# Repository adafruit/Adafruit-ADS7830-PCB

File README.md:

## Adafruit ADS7830 8-Channel 8-Bit ADC with I2C - STEMMA QT / Qwiic PCB

<a href="http://www.adafruit.com/products/5836"><br/>
Click here to purchase one from the Adafruit shop</a>

PCB files for the Adafruit ADS7830 8-Channel 8-Bit ADC with I2C - STEMMA QT / Qwiic. 

Format is EagleCAD schematic and board layout
* https://www.adafruit.com/product/5836

### Description

Many microcontrollers have ADCs these days, for reading analog/resistive sensors like potentiometers, thermistors, LDR light sensors, etc. but sometimes you need MOAR! Or maybe you're using a single board computer like a Raspberry Pi that has no ADCs at all!

The Adafruit ADS7830 8-Channel 8-Bit ADC with I2C is an affordable 8-channel ADC with I2C interface, so it's easy to include with any platform. Wire up to the SDA/SCL pins plus power and ground, only four wires required. If you need more than 8 channels, there's 2 address pins so you could have 4 x 8 = 32 total ADC channels with chain-able Stemma QT cables.

Note that this chip isn't the fanciest ADC on the market: you can get up 70 Ksamples per second (you'll need 3.4MHz I2C speed support for max speed rate), and only 8-bits of resolution, so it's good for rough sensor measurements. For example, this would definitely be a great way to add a ton of potentiometers or flex sensors to a build, but wouldn't be a good match for precision thermistor conversion.

To use it, check out our Arduino library which will quickly let you read from any of the 8 channels as single ended inputs - or you can use differential mode which will use two adjacent pins for the positive and negative references. You can power the board from 3 or 5V power and logic, which will also act as the reference voltage and pullup voltage. Or you can change the reference voltage by cutting the jumper on the back and wiring to the breakout pad, as long as it is less than the power supply.

To get you going fast, we spun up a custom-made PCB in the STEMMA QT form factor, making it easy to interface with. The STEMMA QT connectors on either side are compatible with the SparkFun Qwiic I2C connectors. This allows you to make solderless connections between your development board and the ADS7830 or to chain it with a wide range of other sensors and accessories using a compatible cable.

QT Cable is not included, but we have a variety in the shop.

Comes with a bit of 0.1" standard header in case you want to use it with a breadboard or perfboard.  Four mounting holes for easy attachment.

### License

Adafruit invests time and resources providing this open source design, please support Adafruit and open-source hardware by purchasing products from [Adafruit](https://www.adafruit.com)!

Designed by Limor Fried/Ladyada for Adafruit Industries.

Creative Commons Attribution/Share-Alike, all text above must be included in any redistribution. 
See license.txt for additional details.

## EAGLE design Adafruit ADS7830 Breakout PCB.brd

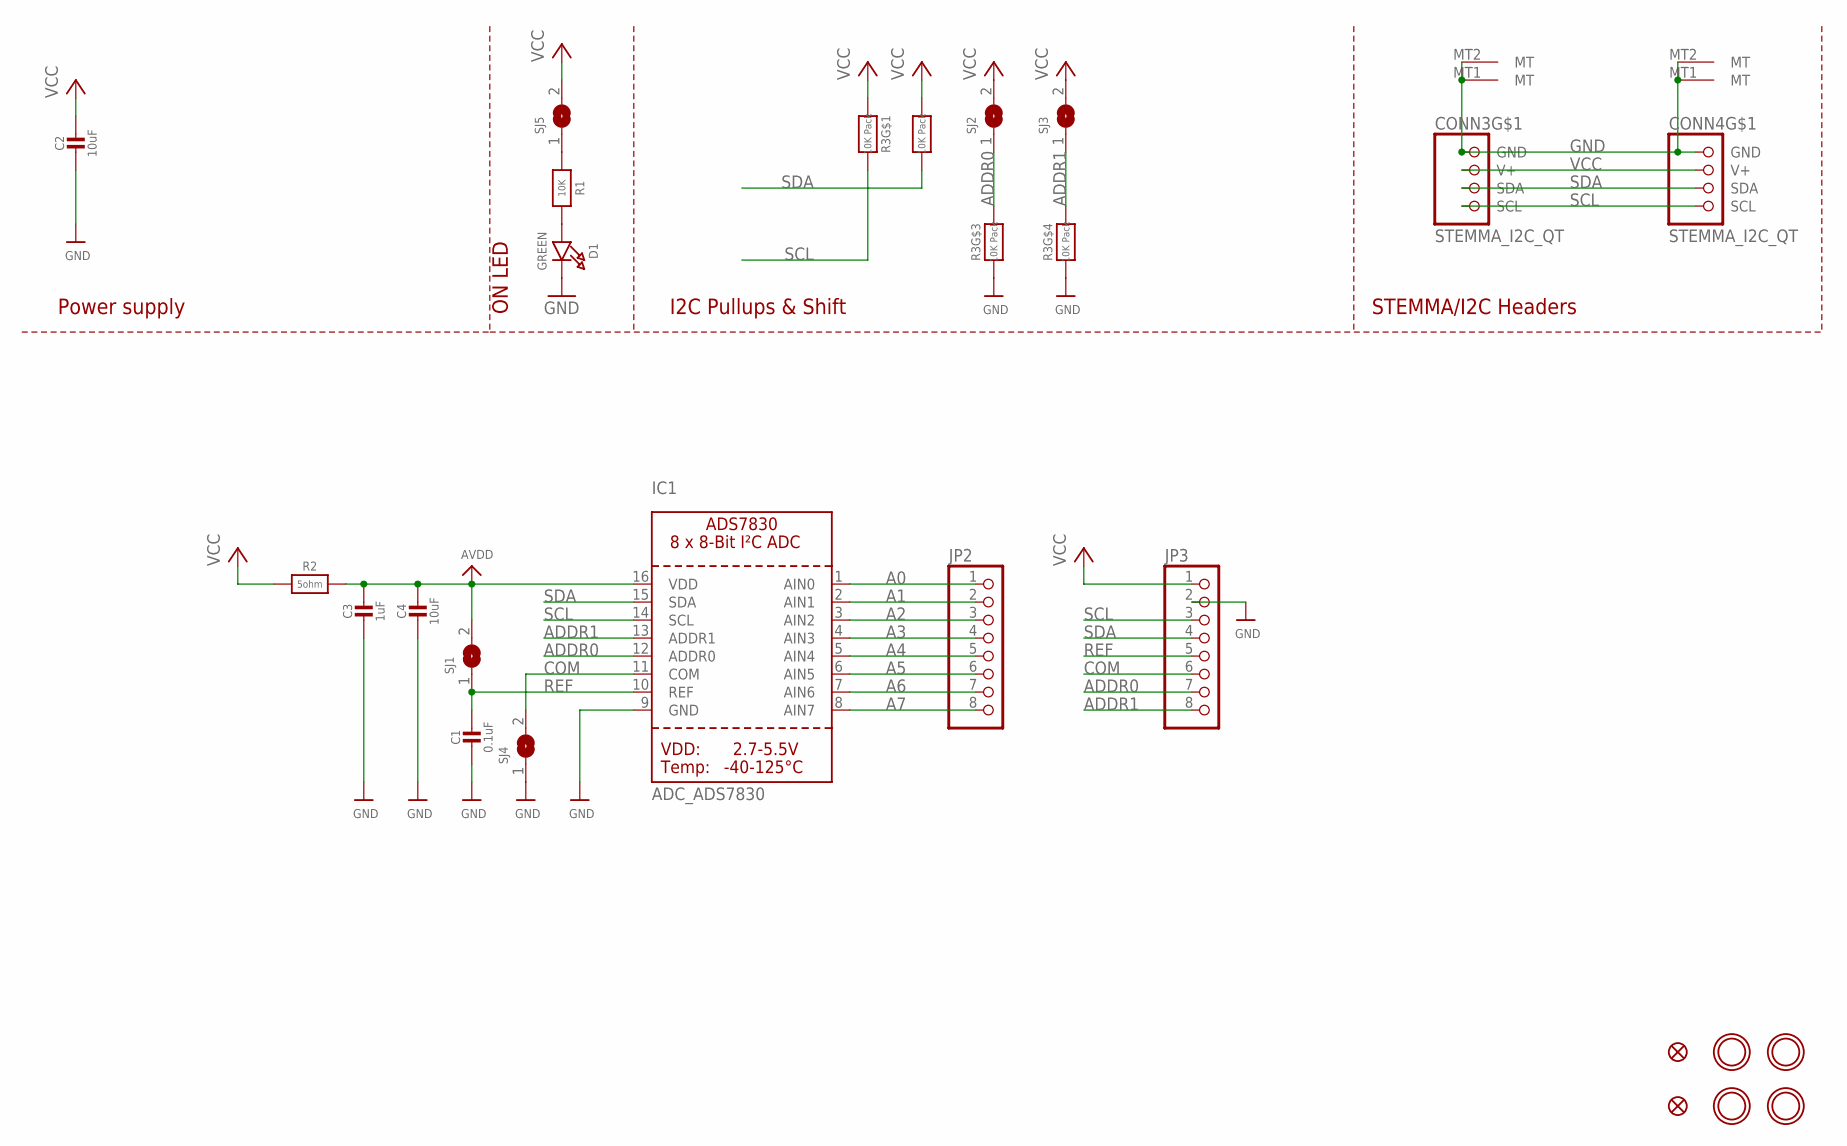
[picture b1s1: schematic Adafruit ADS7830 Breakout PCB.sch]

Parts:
C1: 0.1uF; 0603-NO
C2, C4: 10uF; 0805-NO
C3: 1uF; 0603-NO
CONN3, CONN4: STEMMA_I2C_QT; JST_SH4
D1: GREEN; CHIPLED_0603_NOOUTLINE
FID3, FID4: FIDUCIAL_1MM
IC1: ADC_ADS7830; TSSOP16
JP2, JP3: HEADER-1X870MIL; 1X08_ROUND_70
R1: 10K; 0603-NO
R2: 5ohm; 0603-NO
R3: 10K Pack; RESPACK_4X0603
SJ1, SJ4, SJ5: SOLDERJUMPERCLOSED; SOLDERJUMPER_CLOSEDWIRE
SJ2, SJ3: SOLDERJUMPER; SOLDERJUMPER_ARROW_NOPASTE
U$1, U$17, U$19, U$21: MOUNTINGHOLE2.5; MOUNTINGHOLE_2.5_PLATED

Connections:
A0: IC1.1 (AIN0), JP2.1
A1: IC1.2 (AIN1), JP2.2
A2: IC1.3 (AIN2), JP2.3
A3: IC1.4 (AIN3), JP2.4
A4: IC1.5 (AIN4), JP2.5
A5: IC1.6 (AIN5), JP2.6
A6: IC1.7 (AIN6), JP2.7
A7: IC1.8 (AIN7), JP2.8
ADDR0: IC1.12 (ADDR0), JP3.7, R3.6 (2), SJ2.1
ADDR1: IC1.13 (ADDR1), JP3.8, R3.5 (2), SJ3.1
AVDD: C3.1, C4.1, IC1.16 (VDD), R2.2, SJ1.2
COM: IC1.11 (COM), JP3.6, SJ4.2
GND: C1.2, C2.2, C3.2, C4.2, CONN3.1 (GND), CONN3.MT1 (MT), CONN3.MT2 (MT), CONN4.1 (GND), CONN4.MT1 (MT), CONN4.MT2 (MT), D1.C, IC1.9 (GND), JP3.2, R3.3 (1), R3.4 (1), SJ4.1
unnamed: D1.A, R1.2
unnamed: R1.1, SJ5.1
REF: C1.1, IC1.10 (REF), JP3.5, SJ1.1
SCL: CONN3.4 (SCL), CONN4.4 (SCL), IC1.14 (SCL), JP3.3, R3.8 (2)
SDA: CONN3.3 (SDA), CONN4.3 (SDA), IC1.15 (SDA), JP3.4, R3.7 (2)
VCC: C2.1, CONN3.2 (V+), CONN4.2 (V+), JP3.1, R2.1, R3.1, R3.2 (1), SJ2.2, SJ3.2, SJ5.2

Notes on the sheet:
I2C Pullups & Shift
STEMMA/I2C Headers
ON LED
Power supply

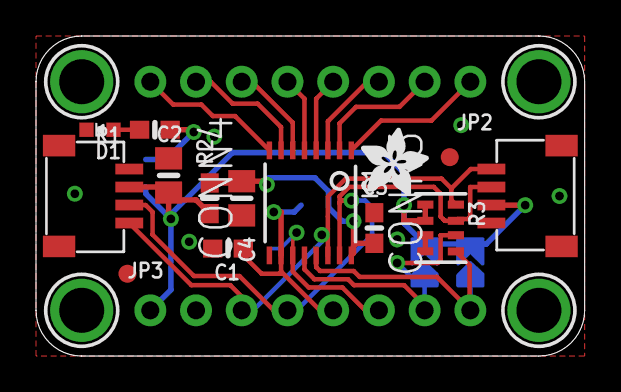
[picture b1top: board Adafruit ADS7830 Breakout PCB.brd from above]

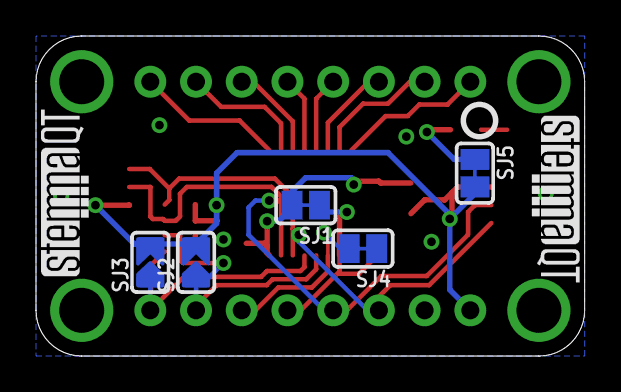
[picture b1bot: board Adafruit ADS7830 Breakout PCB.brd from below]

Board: 2 copper layers, 30.5 x 17.8 mm, 54 parts (16 on the bottom side), 19 nets.

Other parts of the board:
PLABEL0: PLABEL0
PLABEL1: PLABEL1
PLABEL2: PLABEL2
PLABEL3: PLABEL3
PLABEL4: PLABEL4
PLABEL5: PLABEL5
PLABEL6: PLABEL6
PLABEL7: PLABEL7
PLABEL8: PLABEL8
PLABEL9: PLABEL9
PLABEL10: PLABEL10
PLABEL11: PLABEL11
PLABEL12: PLABEL12
PLABEL13: PLABEL13
PLABEL14: PLABEL14
PLABEL15: PLABEL15
PLABEL16: PLABEL16
PLABEL17: PLABEL17
PLABEL18: PLABEL18
PLABEL19: PLABEL19
PLABEL20: PLABEL20
PLABEL21: PLABEL21
PLABEL22: PLABEL22
PLABEL23: PLABEL23
PLABEL24: PLABEL24
PLABEL25: PLABEL25
U$22: ADAFRUIT_3.5MM
U$25: PCBFEAT-REV-040
U$30, U$31: STEMMAQT

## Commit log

2023-11-03 adding cookiecutter output

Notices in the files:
parts and their libraries:
microbuilder: This work is placed in the public domain, and may be freely used for commercial and non-commercial work with the following conditions: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
